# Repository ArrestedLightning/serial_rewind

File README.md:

# Serial Rewind

This project provides an internal serial port to certain PowerPC Macintosh computers that shipped without one built in.  This is accomplished by replacing the internal modem, similar to the GeeThree StealthPort, the Griffin gPort, and Alex Hixon's Jamport.

This project is a work-in-progress.  Any use of the files here is at your own risk.

The goal is to support most PowerPC G3 and G4 machines.  See the README file in the hardware directory for more information on the status of each variant.

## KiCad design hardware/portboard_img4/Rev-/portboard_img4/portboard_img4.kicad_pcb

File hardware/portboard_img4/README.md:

# Portboard IMG4

This is a simple breakout board designed specifically for the iMac G4.  As far as I know, the iMac G4 is the only machine which used this form factor modem port board.  This board was designed based on measurements from an original board, but has not yet been fit-tested in an actual machine.  I can therefore make no guarantees about its usability.

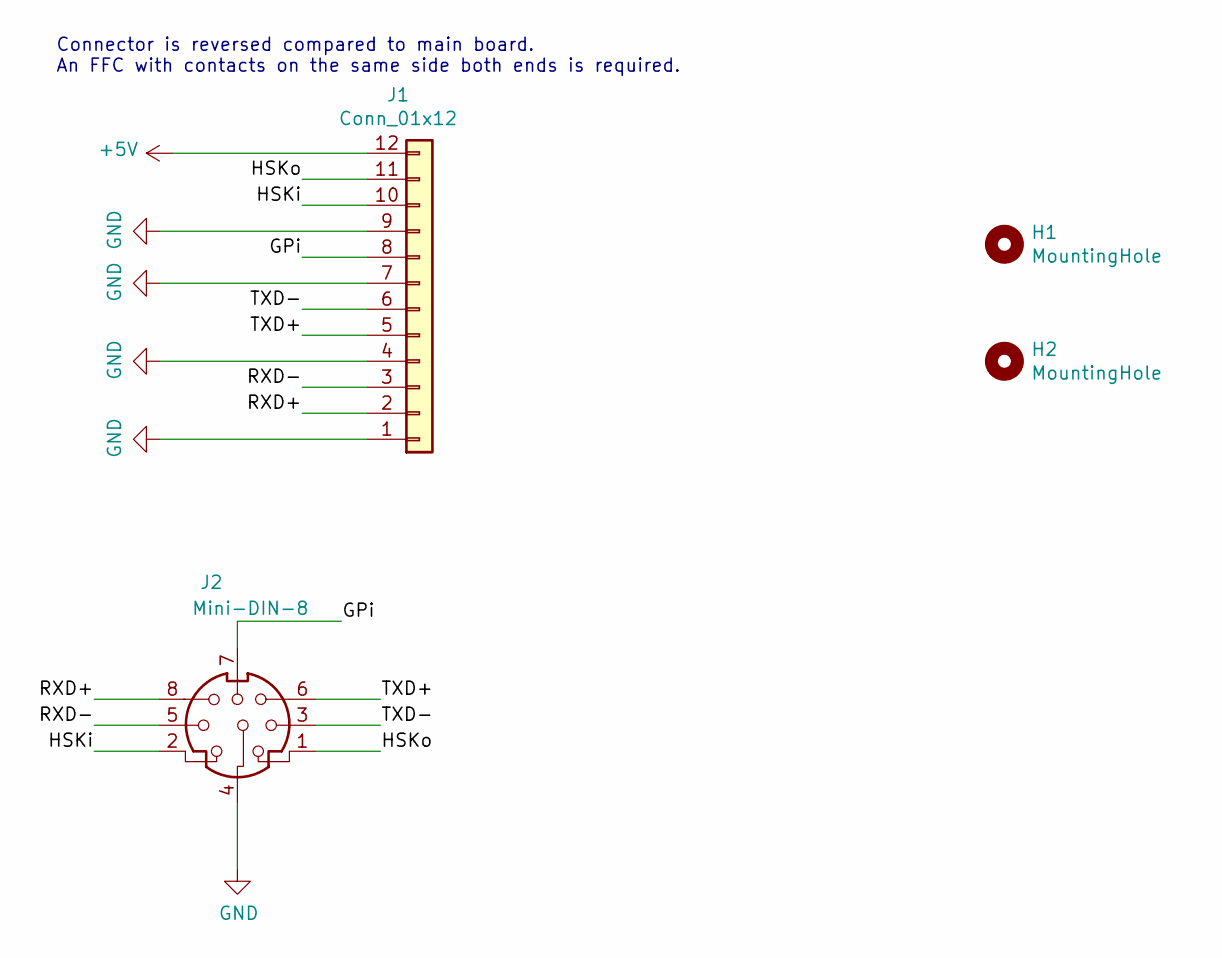
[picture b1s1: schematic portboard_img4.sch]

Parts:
H1, H2: MountingHole; MountingHole_2.2mm_M2_Pad
J1: Conn_01x12; Hirose_FH12-12S-0.5SH_1x12-1MP_P0.50mm_Horizontal
J2: Mini-DIN-8; MINI_DIN8-1H

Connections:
+5V: J1.12
/GPi: J1.8, J2.7
/HSKi: J1.10, J2.2
/HSKo: J1.11, J2.1
/RXD+: J1.2, J2.8
/RXD-: J1.3, J2.5
/TXD+: J1.5, J2.6
/TXD-: J1.6, J2.3
GND: J1.1, J1.4, J1.7, J1.9, J2.4

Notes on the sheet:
Connector is reversed compared to main board. An FFC with contacts on the same side both ends is required.

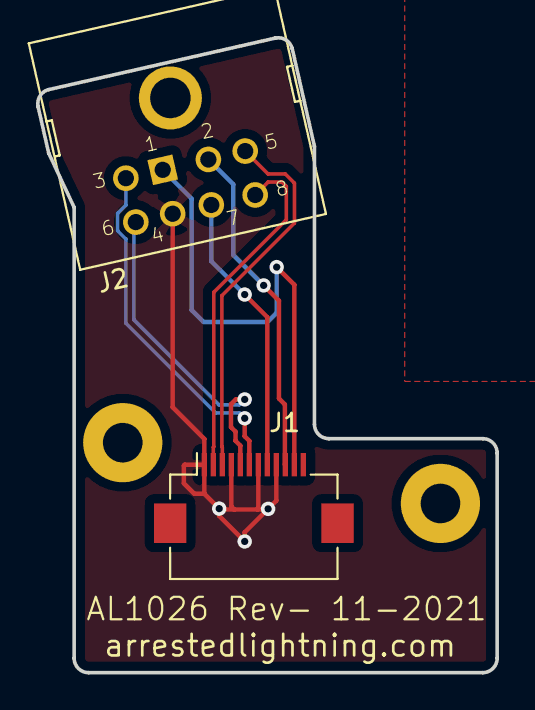
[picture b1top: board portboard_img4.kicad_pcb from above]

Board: 2 copper layers, 25.5 x 35.3 mm, 4 parts (0 on the bottom side), 8 nets.

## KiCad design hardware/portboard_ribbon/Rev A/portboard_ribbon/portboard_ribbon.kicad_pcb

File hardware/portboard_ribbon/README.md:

# Portboard Ribbon

This is a simple breakout board designed to use a pin header connection to a IDC connector on a ribbon cable.  This is not designed to fit in any specific machine; instead, the intention was it could be used on a PCI bracket.  (A 3D-printed mounting bracket would be required, but has not been designed yet.)  I would generally recommend using one of the machine-specfic port breakouts instead when possible, but removing the original modem port non-destructively is not the most straightforward on some machines.  A PCI bracket may be preferred for users who want to keep their machines as close to stock as possible.

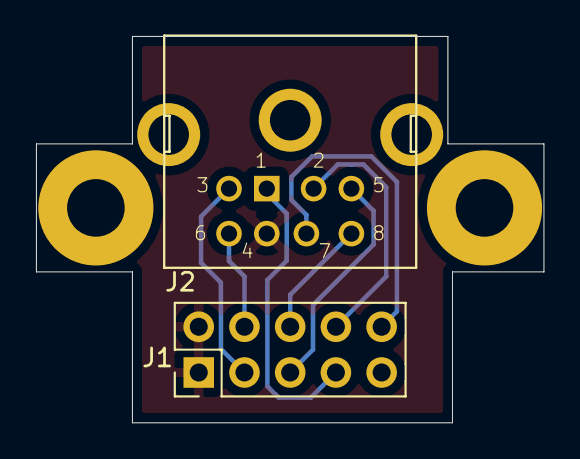
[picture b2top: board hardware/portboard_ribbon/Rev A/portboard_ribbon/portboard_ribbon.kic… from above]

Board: 2 copper layers, 28.2 x 21.5 mm, 4 parts (0 on the bottom side), 8 nets.

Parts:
H1, H2: MountingHole; MountingHole_3.2mm_M3_Pad
J1: Conn_02x05_Odd_Even; PinHeader_2x05_P2.54mm_Vertical
J2: Mini-DIN-8; MINI_DIN8

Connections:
/GPi: J1.10, J2.7
/HSKi: J1.8, J2.2
/HSKo: J1.7, J2.1
/RXD+: J1.6, J2.8
/RXD-: J1.5, J2.5
/TXD+: J1.4, J2.6
/TXD-: J1.3, J2.3
GND: J1.1, J1.2, J2.4

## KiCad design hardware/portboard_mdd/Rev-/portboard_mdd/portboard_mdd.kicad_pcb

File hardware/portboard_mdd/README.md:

# Portboard MDD

This is a simple breakout board designed specifically for the Mirrored Drive Door (MDD) Power Mac G4.  This was an experiment to see if there was an easy way to take advantage of the existing mounting points in the MDD to design a PCB-only replacement for the modem port.  However, it didn't end up being a great solution.  There is only one usable mounting hole built into the case, and the board tends to rotate when plugging in a serial device. I wasn't able to find a great way to anchor the other side of the board besides using a zip tie.  The stock modem port bracket has tabs that lock into the case, but they are too small to realistically 3D print a replacement.  I also had to use a washer to space the board up to the right height.
Given that the stock modem port bracket is reversible to blank off the port if no modem was originally included, I believe that all MDD machines came with a usable bracket.  Therefore, this board is probably of limited use in the vast majority of cases.  The optimum solution going forward will probably be to make an updated portboard_dt design which supports the use of the stock modem bracket.

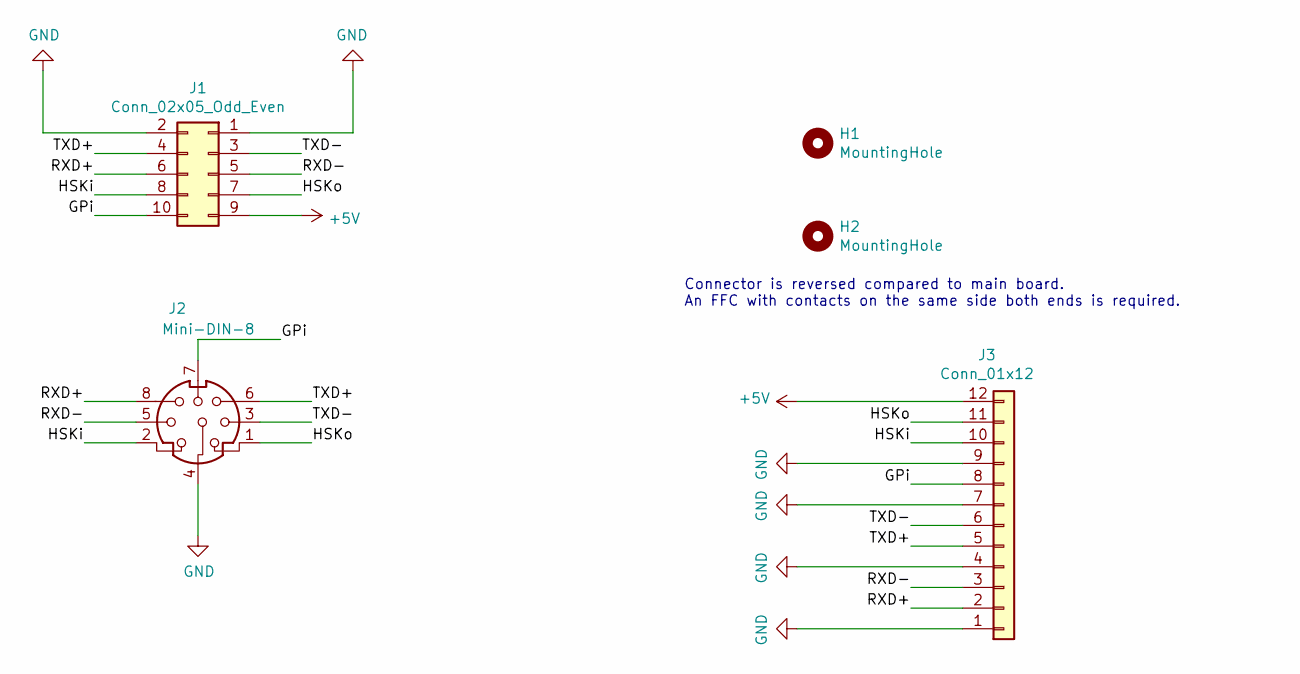
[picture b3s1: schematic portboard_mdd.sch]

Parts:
H1, H2: MountingHole; MountingHole_4mm_Pad
J1: Conn_02x05_Odd_Even; PinHeader_2x05_P2.54mm_Vertical
J2: Mini-DIN-8; MINI_DIN8
J3: Conn_01x12; Hirose_FH12-12S-0.5SH_1x12-1MP_P0.50mm_Horizontal

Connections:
+5V: J1.9, J3.12
/GPi: J1.10, J2.7, J3.8
/HSKi: J1.8, J2.2, J3.10
/HSKo: J1.7, J2.1, J3.11
/RXD+: J1.6, J2.8, J3.2
/RXD-: J1.5, J2.5, J3.3
/TXD+: J1.4, J2.6, J3.5
/TXD-: J1.3, J2.3, J3.6
GND: J1.1, J1.2, J2.4, J3.1, J3.4, J3.7, J3.9

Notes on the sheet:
Connector is reversed compared to main board. An FFC with contacts on the same side both ends is required.

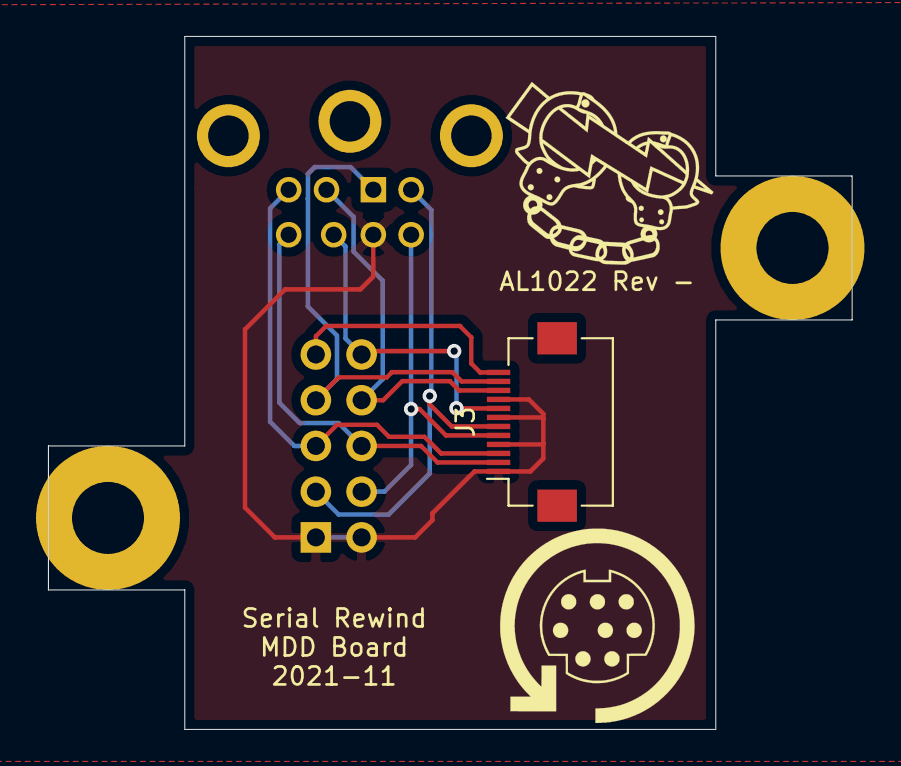
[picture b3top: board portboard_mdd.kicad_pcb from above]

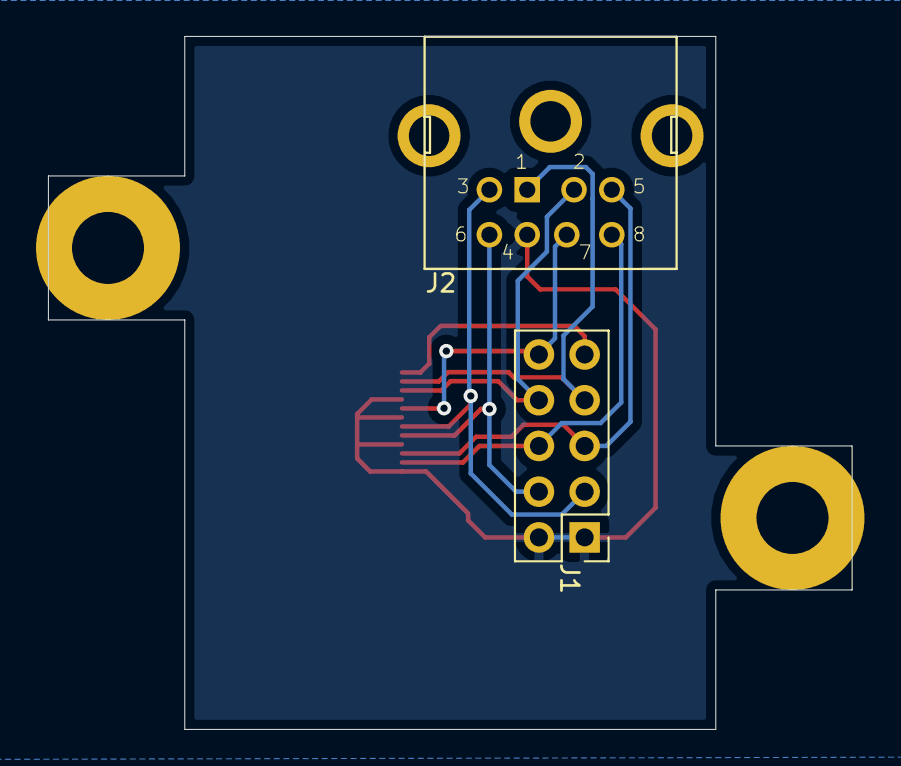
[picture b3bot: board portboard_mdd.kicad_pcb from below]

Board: 2 copper layers, 44.6 x 38.5 mm, 5 parts (2 on the bottom side), 9 nets.

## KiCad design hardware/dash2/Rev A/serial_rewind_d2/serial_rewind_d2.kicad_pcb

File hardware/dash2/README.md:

# "Dash 2" main board

This is the main board for systems which use a "Dash 2" modem board. This covers a large number of the PowerPC Macs, including the Slot load iMac G3, at least some G3 PowerBooks and iBooks, all Power Mac G4s, and the G4 Cube.  The original Dash 2 modem board supported both an onboard modem port and an external one.  This board also supports both an onboard serial port and an external one.  As far as I know, the onboard port was only used on the slot load iMac G3s and the G4 Cube.  I have tested the onboard port on a G4 cube and it fits perfectly;  I have not yet had the chance to test on an iMac.  All other machines will require an external port breakout board to get the serial port out.

The board is designed around the use of vintage GeoPort chips.  Back in the day, several different chips with roughly equivalent functionality were produced by different manufacturers, but they have all been out of production for years.  At the moment, they seem to be relatively easy to obtain, but that may not necessarily be the case going forward.  Therefore, this board has been designed to support multiple different chips.  All of these vintage chips will require a -5V power supply.  Some can generate their own -5V supply, others require an external -5V supply.  Some Macs provide a negative supply which can be used to produce this; others only provide a positive supply which will then need to be inverted.  This technique will also work on Macs that provide a negative supply and is generally preferred for maximum compatibility.  The board supports a number of different voltage and chip combinations by populating different voltage regulator ICs and jumpers.

The choice to use vintage ICs was a deliberate one; their use of a negative supply is significant.  Although it is possible to produce a working RS-422 serial port using modern ICs (as done in the Jamport), the Mac serial port is actually a unique RS-422/RS232 hybrid design that doesn't really have a modern equivalent as far as I can tell.  Without a negative supply, the voltage output will only be 0-5V in RS232 mode.  While this will work with many recent RS-232 devices, there are a number of vintage devices which really only work well if the RS-232 signal levels can swing negative.  Therefore, for maximum compatibility with vintage devices, there really is no substitute for period-correct transceiver ICs.

The Dash 2 connector also provides signals for a USB port.  This board breaks those signals out to a standard USB type A port, which can be mounted horizontally or vertically.  This could be used (for example) for an internal flash drive or Bluetooth adapter.

More information on possible configurations is detailed on the schematic.  Feel free to open an issue if anything is unclear.

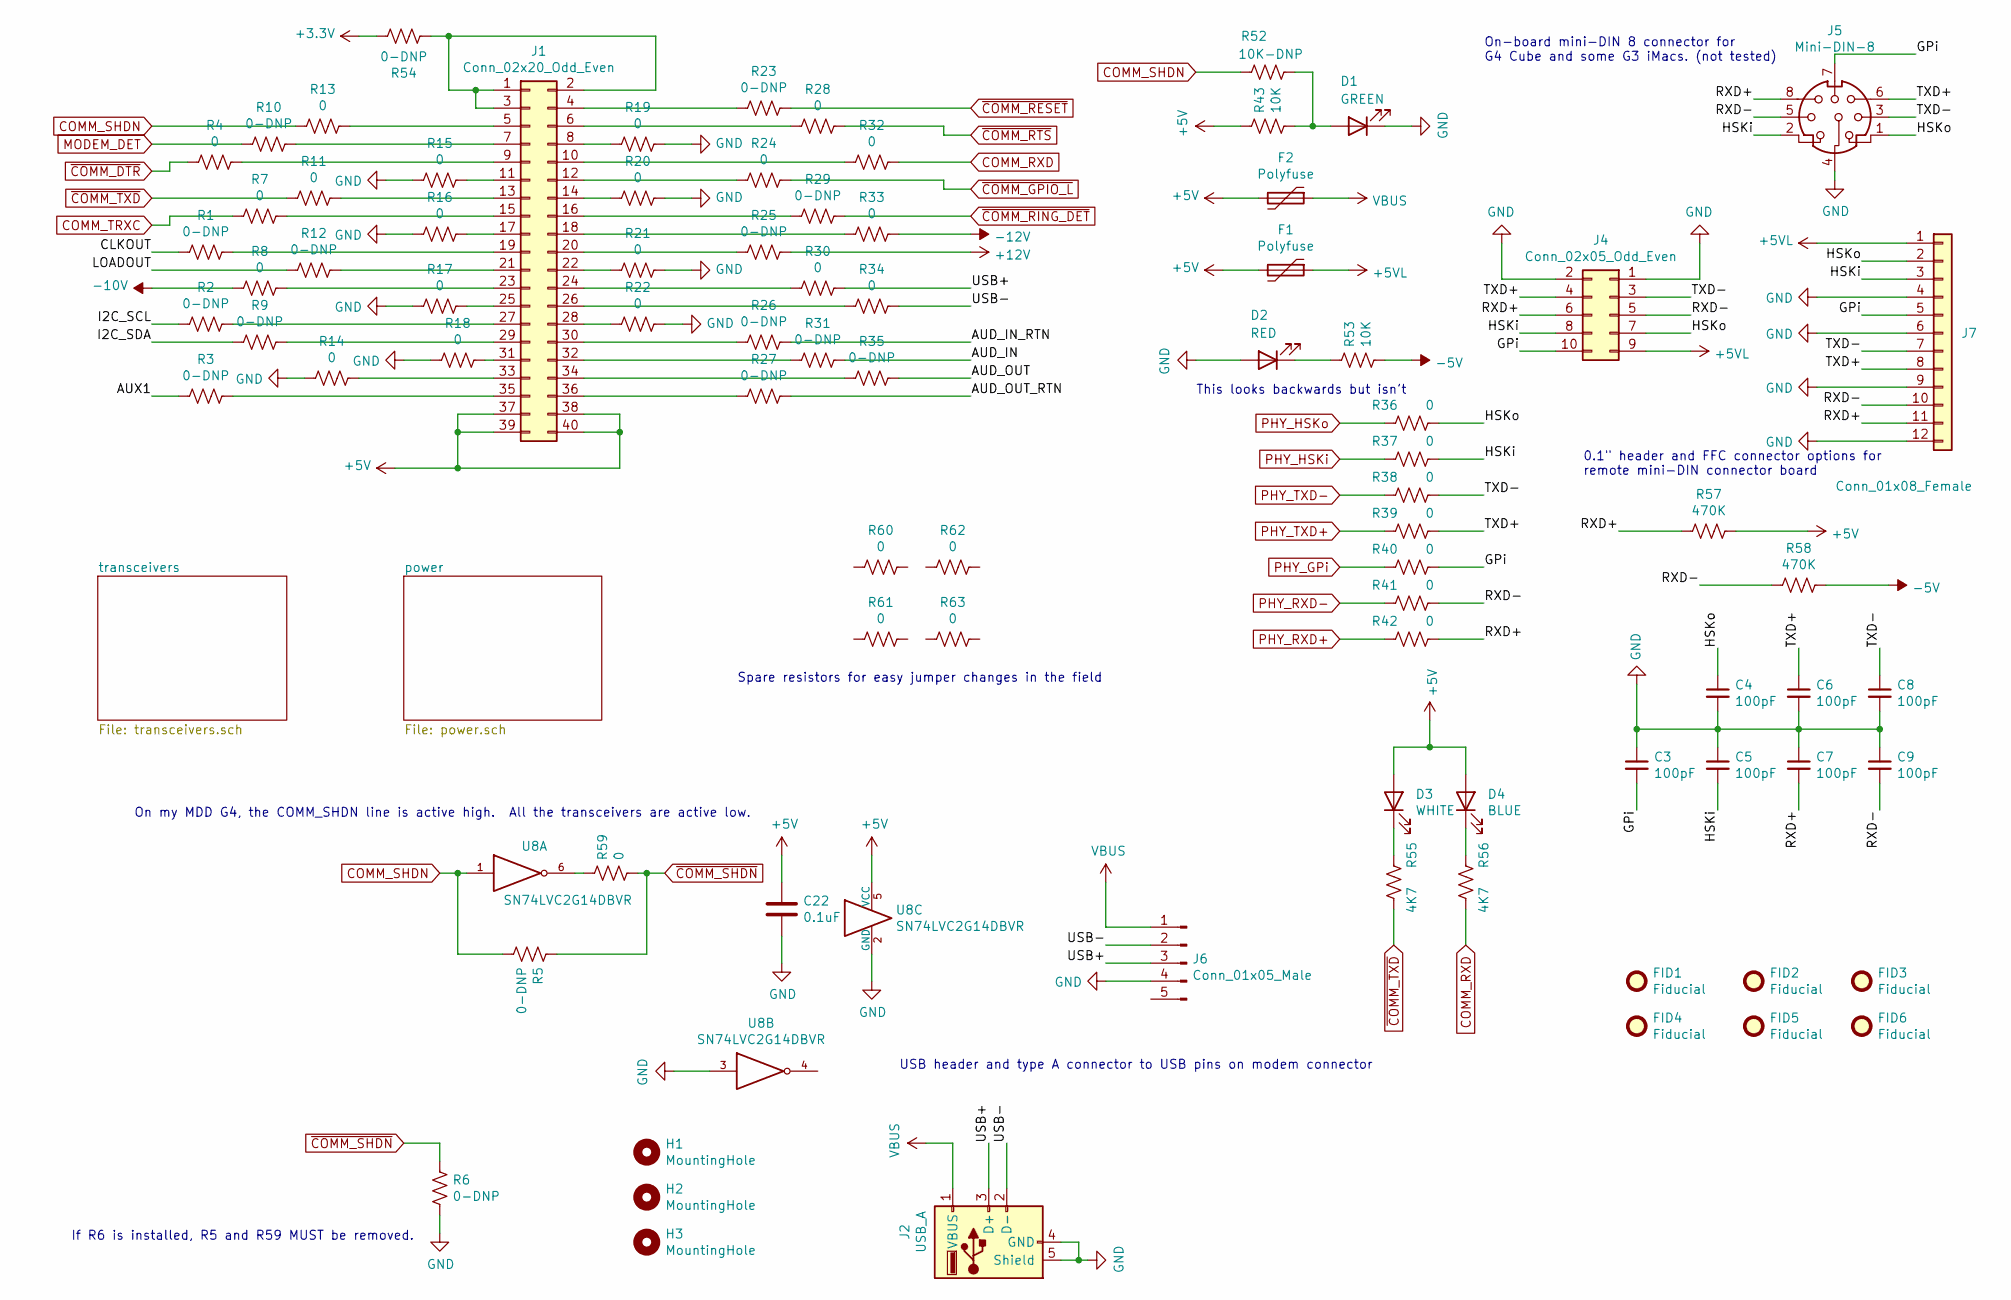
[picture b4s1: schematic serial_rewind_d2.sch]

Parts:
C3, C4, C5, C6, C7, C8, C9: 100pF; C_0603_1608Metric_Pad1.08x0.95mm_HandSolder; JLCPCB C14858
C22: 0.1uF; C_0603_1608Metric_Pad1.08x0.95mm_HandSolder; JLCPCB C14663
D1: GREEN; LED_0805_2012Metric; JLCPCB C2297
D2: RED; LED_0805_2012Metric; JLCPCB C84256
D3: WHITE; LED_0805_2012Metric; JLCPCB C34499
D4: BLUE; LED_0805_2012Metric; JLCPCB C2293
F1, F2: Polyfuse; Fuse_0805_2012Metric_Pad1.15x1.40mm_HandSolder; JLCPCB C70057
FID1, FID2, FID3, FID4, FID5, FID6: Fiducial; Fiducial_1mm_Mask2mm
H1, H2, H3: MountingHole; MountingHole_3.2mm_M3_Pad
J1: Conn_02x20_Odd_Even; 0528850474; Digikey WM3397CT-ND
J2: USB_A; USB_A_HORIZ_VERT_COMBO
J4: Conn_02x05_Odd_Even; PinHeader_2x05_P2.54mm_Vertical; Digikey 2057-PH2-10-UA-ND
J5: Mini-DIN-8; MINI_DIN8; Digikey 2057-MDJ-008-FS-ND
J6: Conn_01x05_Male; PinSocket_1x05_P2.54mm_Vertical
J7: Conn_01x08_Female; Hirose_FH12-12S-0.5SH_1x12-1MP_P0.50mm_Horizontal
R1, R2, R3, R5, R6, R9, R10, R12, R23, R25, R26, R27, R29, R31, R35, R54: 0-DNP; R_0603_1608Metric_Pad0.98x0.95mm_HandSolder; Digikey RMCF0603ZT0R00CT-ND
R4, R7, R8, R11, R13, R14, R15, R16, R17, R18, R19, R20, R21, R22, R24, R28, R30, R32, R33, R34, R36, R37, R38, R39, R40, R41, R42, R60, R61, R62, R63: 0; R_0603_1608Metric_Pad0.98x0.95mm_HandSolder; JLCPCB C21189
R43, R53: 10K; R_0603_1608Metric_Pad0.98x0.95mm_HandSolder; JLCPCB C25804
R52: 10K-DNP; R_0603_1608Metric_Pad0.98x0.95mm_HandSolder; Digikey RMCF0603JT10K0CT-ND
R55, R56: 4K7; R_0603_1608Metric_Pad0.98x0.95mm_HandSolder; JLCPCB C23162
R57, R58: 470K; R_0603_1608Metric_Pad0.98x0.95mm_HandSolder; Digikey RMCF0603FT470KCT-ND
R59: 0; R_0603_1608Metric_Pad0.98x0.95mm_HandSolder; Digikey RMCF0603ZT0R00CT-ND
U8: SN74LVC2G14DBVR; SOT-23-6_Handsoldering; Digikey 296-13010-1-ND

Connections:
+3V3: R54.1
+5V: C22.1, D3.2 (A), D4.2 (A), F1.2, F2.2, J1.37, J1.38, J1.39, J1.40, R43.1, R57.1, U8.5 (VCC); also elsewhere on the board
+5VL: F1.1, J4.9, J7.1
+12V: R25.1
-5V: R53.2, R58.1; also elsewhere on the board
-10V: R8.2; also elsewhere on the board
-12V: R33.1; also elsewhere on the board
/AUD_IN: R31.1
/AUD_IN_RTN: R26.1
/AUD_OUT: R35.1
/AUD_OUT_RTN: R27.1
/AUX1: R3.2
/CLKOUT: R1.2
/GPi: C3.2, J4.10, J5.7, J7.5, R40.1
/HSKi: C5.2, J4.8, J5.2, J7.3, R37.1
/HSKo: C4.1, J4.7, J5.1, J7.2, R36.1
/I2C_SCL: R2.2
/I2C_SDA: R9.2
/LOADOUT: R12.2
/RXD+: C7.2, J4.6, J5.8, J7.11, R42.1, R57.2
/RXD-: C9.2, J4.5, J5.5, J7.10, R41.1, R58.2
/TXD+: C6.1, J4.4, J5.6, J7.8, R39.1
/TXD-: C8.1, J4.3, J5.3, J7.7, R38.1
/USB+: J2.3 (D+), J6.3, R30.1
/USB-: J2.2 (D-), J6.2, R34.1
COMM_RXD: R32.1, R56.1; also elsewhere on the board
COMM_SHDN: R5.1, R13.2, R52.1, U8.1; also elsewhere on the board
COMM_TRXC: R7.2; also elsewhere on the board
GND: C3.1, C4.2, C5.1, C6.2, C7.1, C8.2, C9.1, C22.2, D1.1 (K), D2.2 (A), J2.4 (GND), J2.5 (Shield), J4.1, J4.2, J5.4, J6.4, J7.4, J7.6, J7.9, J7.12, R6.1, R14.2, R15.2, R16.2, R17.2, R18.2, R19.1, R20.1, R21.1, R22.1, U8.2 (GND), U8.3; also elsewhere on the board
MODEM_DET: R10.2
unnamed: D1.2 (A), R43.2, R52.2
unnamed: D2.1 (K), R53.1
unnamed: D3.1 (K), R55.2
unnamed: D4.1 (K), R56.2
unnamed: J1.1, J1.2, J1.3, R54.2
unnamed: J1.4, R23.2
unnamed: J1.5, R13.1
unnamed: J1.6, R28.2
unnamed: J1.7, R10.1
unnamed: J1.8, R19.2
unnamed: J1.9, R4.1
unnamed: J1.10, R32.2
unnamed: J1.11, R15.1
unnamed: J1.12, R24.2
unnamed: J1.13, R11.1
unnamed: J1.14, R20.2
unnamed: J1.15, R7.1
unnamed: J1.16, R29.2
unnamed: J1.17, R16.1
unnamed: J1.18, R33.2
unnamed: J1.19, R1.1
unnamed: J1.20, R25.2
unnamed: J1.21, R12.1
unnamed: J1.22, R21.2
unnamed: J1.23, R8.1
unnamed: J1.24, R30.2
unnamed: J1.25, R17.1
unnamed: J1.26, R34.2
unnamed: J1.27, R2.1
unnamed: J1.28, R22.2
unnamed: J1.29, R9.1
unnamed: J1.30, R26.2
unnamed: J1.31, R18.1
unnamed: J1.32, R31.2
unnamed: J1.33, R14.1
unnamed: J1.34, R35.2
unnamed: J1.35, R3.1
unnamed: J1.36, R27.2
unnamed: R59.2, U8.6
PHY_GPi: R40.2; also elsewhere on the board
PHY_HSKi: R37.2; also elsewhere on the board
PHY_HSKo: R36.2; also elsewhere on the board
PHY_RXD+: R42.2; also elsewhere on the board
PHY_RXD-: R41.2; also elsewhere on the board
PHY_TXD+: R39.2; also elsewhere on the board
PHY_TXD-: R38.2; also elsewhere on the board
VBUS: F2.1, J2.1 (VBUS), J6.1
~COMM_DTR: R4.2; also elsewhere on the board
~COMM_GPIO_L: R24.1; also elsewhere on the board
~COMM_RESET: R23.1
~COMM_RING_DET: R29.1
~COMM_RTS: R28.1; also elsewhere on the board
~COMM_SHDN: R5.2, R6.2, R59.1; also elsewhere on the board
~COMM_TXD: R11.2, R55.1; also elsewhere on the board

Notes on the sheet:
On-board mini-DIN 8 connector for G4 Cube and some G3 iMacs. (not tested)
0.1" header and FFC connector options for remote mini-DIN connector board
If R6 is installed, R5 and R59 MUST be removed.
USB header and type A connector to USB pins on modem connector
This looks backwards but isn't
On my MDD G4, the COMM_SHDN line is active high. All the transceivers are active low.
Spare resistors for easy jumper changes in the field

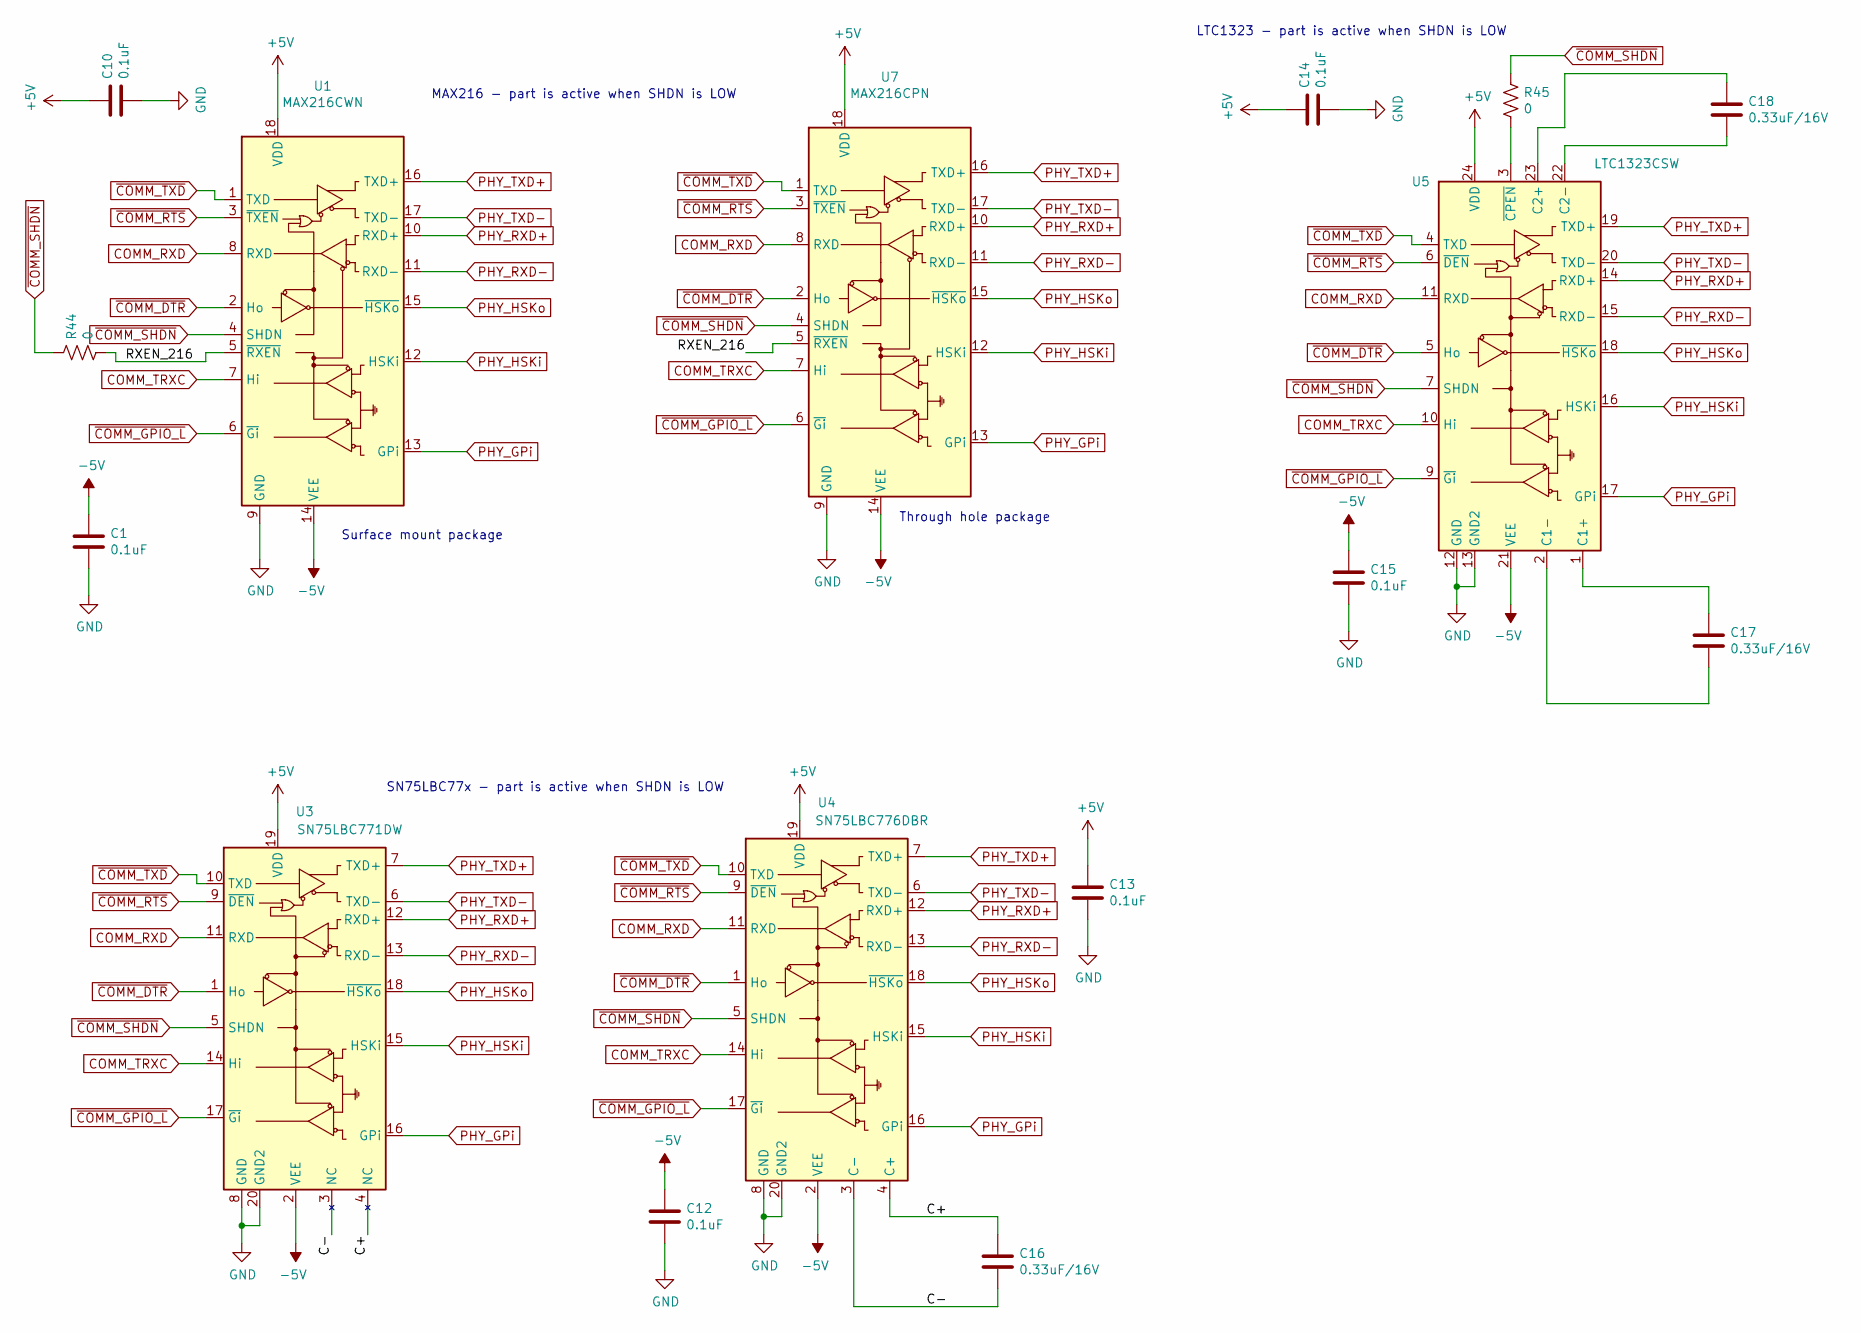
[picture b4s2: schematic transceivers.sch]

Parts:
C1, C10, C12, C13, C14, C15: 0.1uF; C_0603_1608Metric_Pad1.08x0.95mm_HandSolder; JLCPCB C14663
C16, C17, C18: 0.33uF/16V; C_0805_2012Metric_Pad1.18x1.45mm_HandSolder; JLCPCB C1740
R44, R45: 0; R_0603_1608Metric_Pad0.98x0.95mm_HandSolder; JLCPCB C21189
U1: MAX216CWN; SOIC-18W_7.5x11.6mm_P1.27mm; Digikey MAX216CWN+-ND
U3: SN75LBC771DW; SOP-20_7.5x12.8mm_P1.27mm
U4: SN75LBC776DBR; SSOP-20_5.3x7.2mm_P0.65mm
U5: LTC1323CSW; SOP-24_7.5x15.4mm_P1.27mm
U7: MAX216CPN; DIP-18_W7.62mm

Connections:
+5V: C10.1, C13.1, C14.1, U1.18 (VDD), U3.19 (VDD), U4.19 (VDD), U5.24 (VDD), U7.18 (VDD); also elsewhere on the board
-5V: C1.1, C12.1, C15.1, U1.14 (VEE), U3.2 (VEE), U4.2 (VEE), U5.21 (VEE), U7.14 (VEE); also elsewhere on the board
/transceivers/C+: C16.1, U3.4 (NC), U4.4 (C+)
/transceivers/C-: C16.2, U3.3 (NC), U4.3 (C-)
/transceivers/RXEN_216: R44.1, U1.5 (~RXEN), U7.5 (~RXEN)
COMM_RXD: U1.8 (RXD), U3.11 (RXD), U4.11 (RXD), U5.11 (RXD), U7.8 (RXD); also elsewhere on the board
COMM_TRXC: U1.7 (Hi), U3.14 (Hi), U4.14 (Hi), U5.10 (Hi), U7.7 (Hi); also elsewhere on the board
GND: C1.2, C10.2, C12.2, C13.2, C14.2, C15.2, U1.9 (GND), U3.8 (GND), U3.20 (GND2), U4.8 (GND), U4.20 (GND2), U5.12 (GND), U5.13 (GND2), U7.9 (GND); also elsewhere on the board
unnamed: C17.1, U5.1 (C1+)
unnamed: C17.2, U5.2 (C1-)
unnamed: C18.1, U5.23 (C2+)
unnamed: C18.2, U5.22 (C2-)
unnamed: R45.1, U5.3 (~CPEN)
PHY_GPi: U1.13 (GPi), U3.16 (GPi), U4.16 (GPi), U5.17 (GPi), U7.13 (GPi); also elsewhere on the board
PHY_HSKi: U1.12 (HSKi), U3.15 (HSKi), U4.15 (HSKi), U5.16 (HSKi), U7.12 (HSKi); also elsewhere on the board
PHY_HSKo: U1.15 (~HSKo), U3.18 (~HSKo), U4.18 (~HSKo), U5.18 (~HSKo), U7.15 (~HSKo); also elsewhere on the board
PHY_RXD+: U1.10 (RXD+), U3.12 (RXD+), U4.12 (RXD+), U5.14 (RXD+), U7.10 (RXD+); also elsewhere on the board
PHY_RXD-: U1.11 (RXD-), U3.13 (RXD-), U4.13 (RXD-), U5.15 (RXD-), U7.11 (RXD-); also elsewhere on the board
PHY_TXD+: U1.16 (TXD+), U3.7 (TXD+), U4.7 (TXD+), U5.19 (TXD+), U7.16 (TXD+); also elsewhere on the board
PHY_TXD-: U1.17 (TXD-), U3.6 (TXD-), U4.6 (TXD-), U5.20 (TXD-), U7.17 (TXD-); also elsewhere on the board
~COMM_DTR: U1.2 (Ho), U3.1 (Ho), U4.1 (Ho), U5.5 (Ho), U7.2 (Ho); also elsewhere on the board
~COMM_GPIO_L: U1.6 (~Gi), U3.17 (~Gi), U4.17 (~Gi), U5.9 (~Gi), U7.6 (~Gi); also elsewhere on the board
~COMM_RTS: U1.3 (~TXEN), U3.9 (~DEN), U4.9 (~DEN), U5.6 (~DEN), U7.3 (~TXEN); also elsewhere on the board
~COMM_SHDN: R44.2, R45.2, U1.4 (SHDN), U3.5 (SHDN), U4.5 (SHDN), U5.7 (SHDN), U7.4 (SHDN); also elsewhere on the board
~COMM_TXD: U1.1 (TXD), U3.10 (TXD), U4.10 (TXD), U5.4 (TXD), U7.1 (TXD); also elsewhere on the board

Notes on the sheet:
Surface mount package
Through hole package
MAX216 - part is active when SHDN is LOW
LTC1323 - part is active when SHDN is LOW
SN75LBC77x - part is active when SHDN is LOW

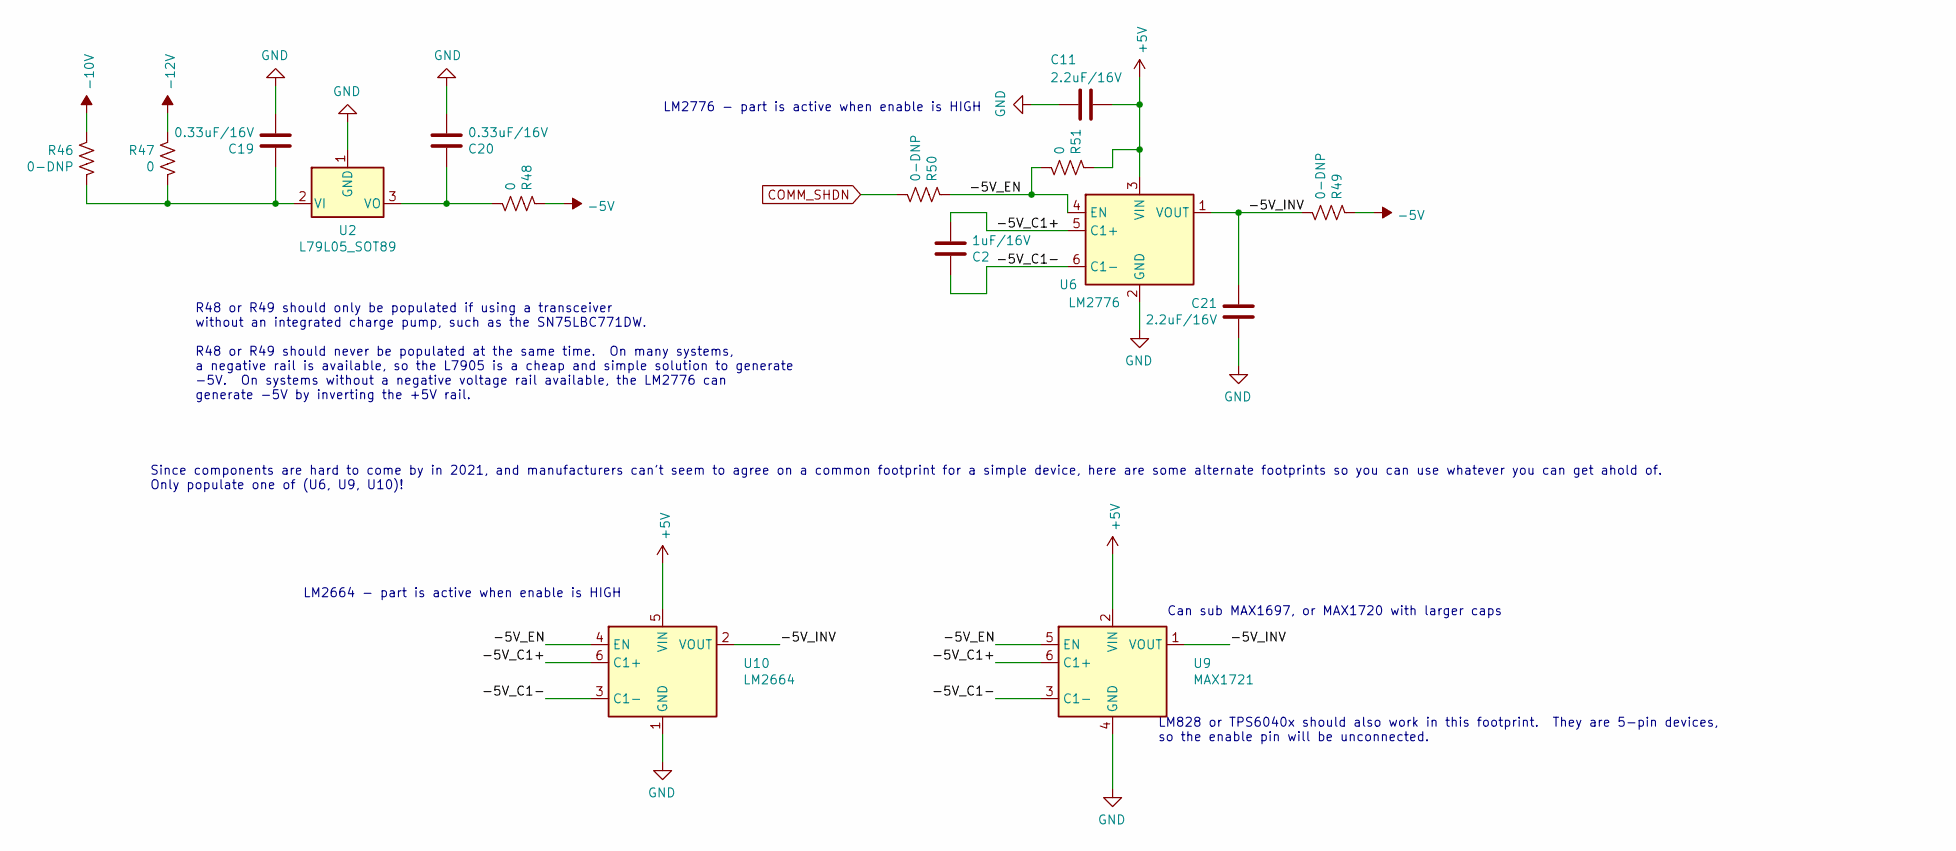
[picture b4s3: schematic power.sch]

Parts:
C2: 1uF/16V; C_0805_2012Metric_Pad1.18x1.45mm_HandSolder; JLCPCB C28323
C11, C21: 2.2uF/16V; C_0805_2012Metric_Pad1.18x1.45mm_HandSolder; JLCPCB C49217
C19, C20: 0.33uF/16V; C_0805_2012Metric_Pad1.18x1.45mm_HandSolder; JLCPCB C1740
R46, R49, R50: 0-DNP; R_0603_1608Metric_Pad0.98x0.95mm_HandSolder; Digikey RMCF0603ZT0R00CT-ND
R47: 0; R_0603_1608Metric_Pad0.98x0.95mm_HandSolder; Digikey RMCF0603ZT0R00CT-ND
R48, R51: 0; R_0603_1608Metric_Pad0.98x0.95mm_HandSolder; JLCPCB C21189
U2: L79L05_SOT89; SOT-89-3; JLCPCB DNP-C842820
U6: LM2776; SOT-23-6_Handsoldering; JLCPCB C840110
U9: MAX1721; SOT-23-6_Handsoldering; JLCPCB C242523
U10: LM2664; SOT-23-6_Handsoldering; JLCPCB C840095

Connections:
+5V: C11.1, R51.2, U6.3 (VIN), U9.2 (VIN), U10.5 (VIN); also elsewhere on the board
-5V: R48.2, R49.2; also elsewhere on the board
-10V: R46.2; also elsewhere on the board
-12V: R47.2; also elsewhere on the board
/power/-5V_C1+: C2.2, U6.5 (C1+), U9.6 (C1+), U10.6 (C1+)
/power/-5V_C1-: C2.1, U6.6 (C1-), U9.3 (C1-), U10.3 (C1-)
/power/-5V_EN: R50.2, R51.1, U6.4 (EN), U9.5 (EN), U10.4 (EN)
/power/-5V_INV: C21.1, R49.1, U6.1 (VOUT), U9.1 (VOUT), U10.2 (VOUT)
COMM_SHDN: R50.1; also elsewhere on the board
GND: C11.2, C19.2, C20.2, C21.2, U2.1 (GND), U6.2 (GND), U9.4 (GND), U10.1 (GND); also elsewhere on the board
unnamed: C19.1, R46.1, R47.1, U2.2 (VI)
unnamed: C20.1, R48.1, U2.3 (VO)

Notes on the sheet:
R48 or R49 should only be populated if using a transceiver without an integrated charge pump, such as the SN75LBC771DW. R48 or R49 should never be populated at the same time. On many systems, a negative rail is available, so the L7905 is a cheap and simple solution to generate -5V. On systems witho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
LM2776 - part is active when enable is HIGH
Can sub MAX1697, or MAX1720 with larger caps
Since components are hard to come by in 2021, and manufacturers can't seem to agree on a common footprint for a simple device, here are some alternate footprints so you can use whatever you can get ahold of. Only populate one of (U6, U9, U10)!
LM828 or TPS6040x should also work in this footprint. They are 5-pin devices, so the enable pin will be unconnected.
LM2664 - part is active when enable is HIGH

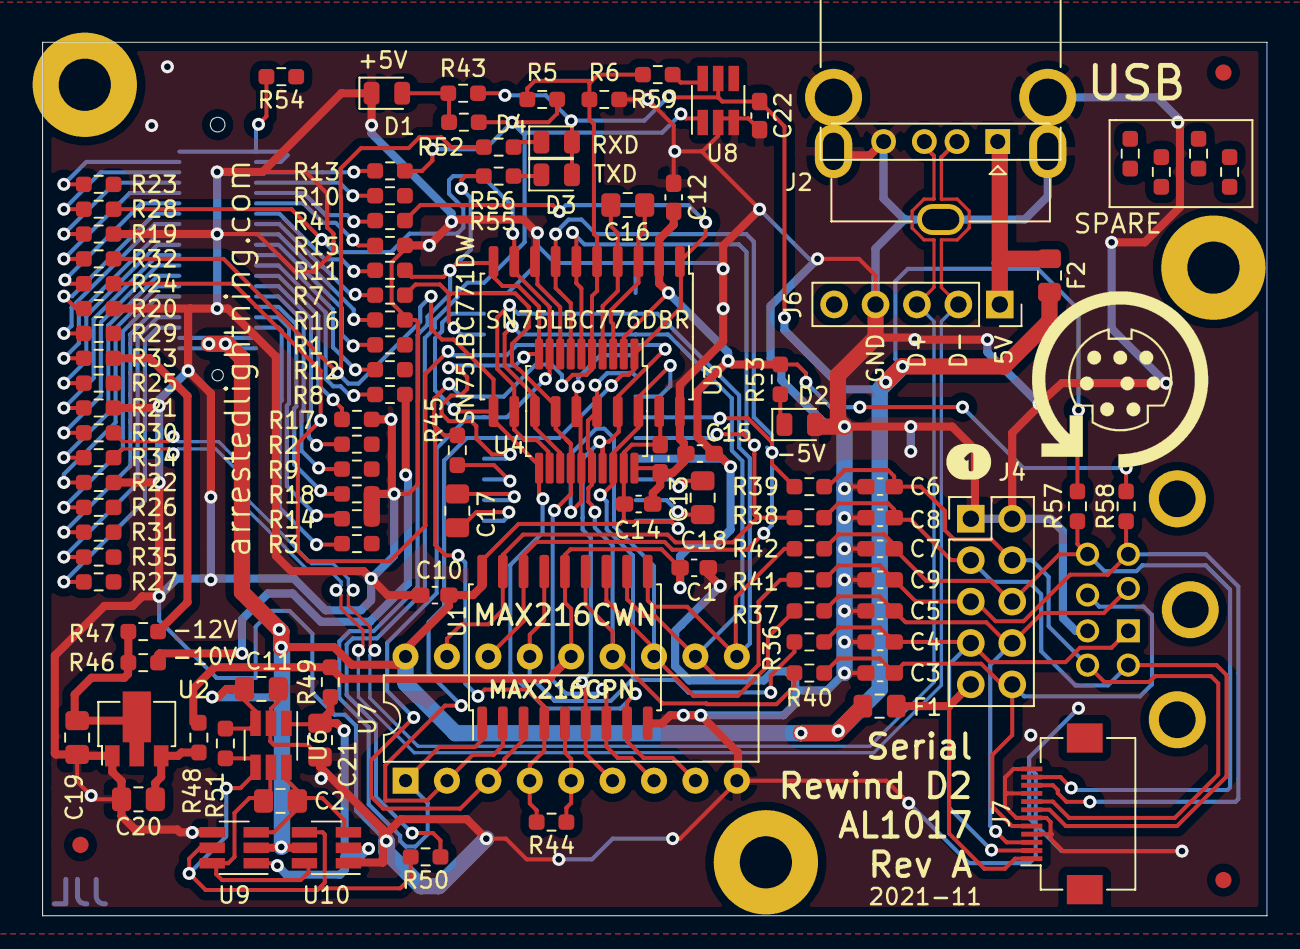
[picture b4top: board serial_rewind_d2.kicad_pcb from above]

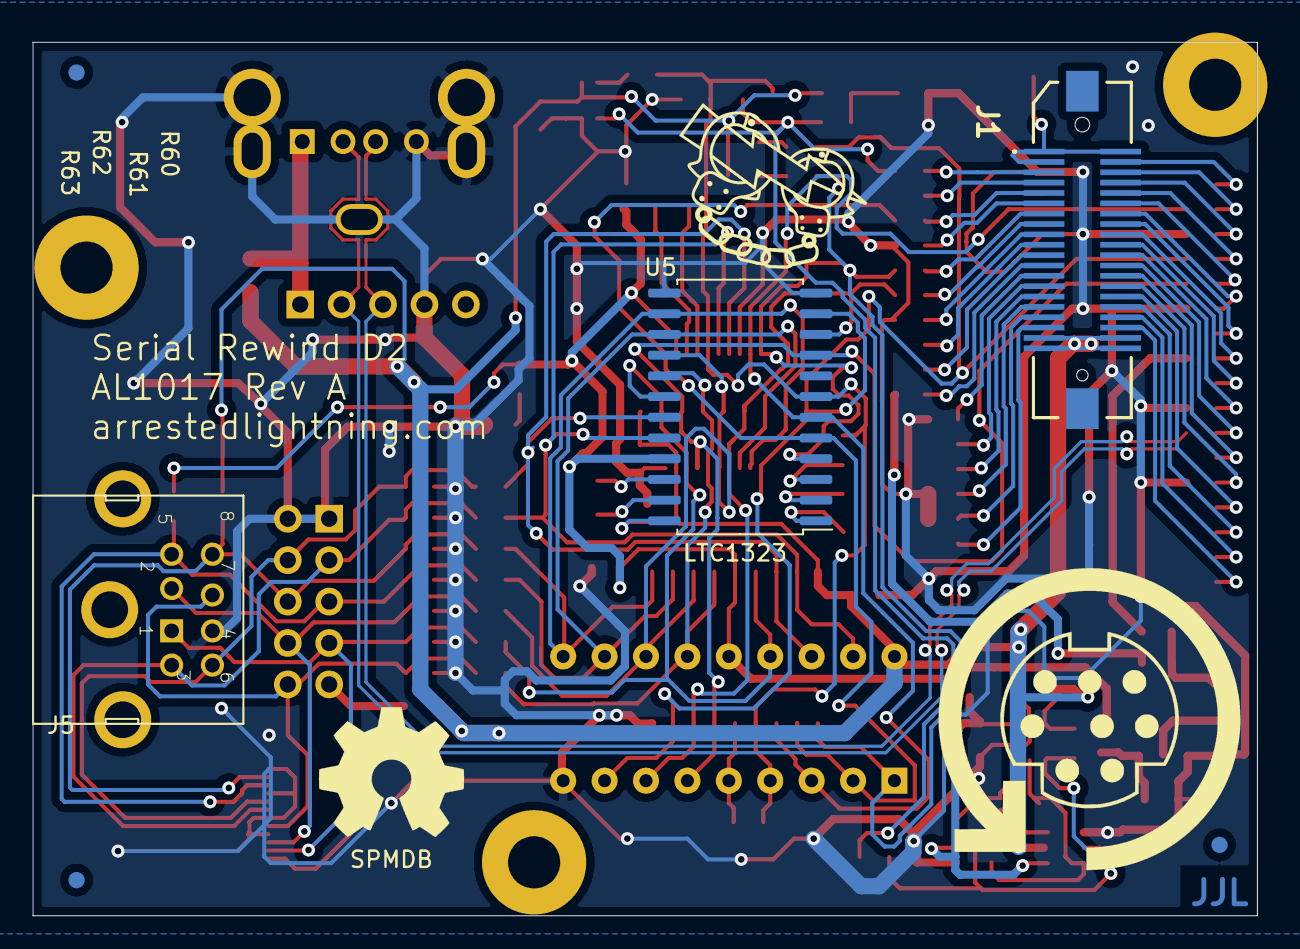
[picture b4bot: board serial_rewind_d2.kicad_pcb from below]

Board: 2 copper layers, 75.1 x 53.6 mm, 117 parts (6 on the bottom side), 84 nets.

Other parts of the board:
kibuzzard-619185EE: G***; label

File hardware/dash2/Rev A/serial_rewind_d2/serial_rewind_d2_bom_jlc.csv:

"Comment","Designator","Footprint","LCSC Part #"
"1uF/16V","C2","C_0805_2012Metric_Pad1.18x1.45mm_HandSolder","C28323"
"100pF","C4,C6,C8,C5,C7,C3,C9","C_0603_1608Metric_Pad1.08x0.95mm_HandSolder","C14858"
"2.2uF/16V","C11,C21","C_0805_2012Metric_Pad1.18x1.45mm_HandSolder","C49217"
"0.33uF/16V","C18,C17,C16,C19,C20","C_0805_2012Metric_Pad1.18x1.45mm_HandSolder","C1740"
"0.1uF","C22,C13,C10,C14,C12,C1,C15","C_0603_1608Metric_Pad1.08x0.95mm_HandSolder","C14663"
"GREEN","D1","LED_0805_2012Metric","C2297"
"RED","D2","LED_0805_2012Metric","C84256"
"WHITE","D3","LED_0805_2012Metric","C34499"
"BLUE","D4","LED_0805_2012Metric","C2293"
"Polyfuse","F2,F1","Fuse_0805_2012Metric_Pad1.15x1.40mm_HandSolder","C70057"
"0","R28,R32,R24,R33,R30,R34,R13,R4,R11,R7,R8,R19,R20,R21,R22,R15,R16,R17,R18,R14,R37,R38,R39,R40,R41,R36,R42,R59,R62,R60,R63,R61,R44,R45,R51,R47,R48","R_0603_1608Metric_Pad0.98x0.95mm_HandSolder","C21189"
"10K","R43,R53","R_0603_1608Metric_Pad0.98x0.95mm_HandSolder","C25804"
"4K7","R55,R56","R_0603_1608Metric_Pad0.98x0.95mm_HandSolder","C23162"
"470K","R57,R58","R_0603_1608Metric_Pad0.98x0.95mm_HandSolder","C23178"
"LM2776","U6","SOT-23-6_Handsoldering","C840110"
"SN74LVC2G14DBVR","U8","SOT-23-6_Handsoldering","C12401"
"MAX1721","U9","SOT-23-6_Handsoldering","C242523"
"LM2664","U10","SOT-23-6_Handsoldering","C840095"
